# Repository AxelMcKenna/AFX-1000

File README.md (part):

# AFX-1000

**Proprietary — all rights reserved.** Original project code, firmware, PCB and housing designs require a separate written license for reuse, builds, manufacture or redistribution. Public access and build instructions do not grant that permission. Third-party licenses and GitHub's applicable platform permissions remain in effect. See [LICENSE](LICENSE) and [dependency notices](THIRD_PARTY_NOTICES.md).

**AFX-1000** is an RMX-1000-inspired effects processor built around a shared C++20 audio engine, available as a native Mac app, AU and VST3. The standalone hardware design uses **Daisy Seed 3 and two main custom PCBs**—signal and power/protection—in a proposed custom housing.

Use it with rekordbox through app capture or an audio interface. The effects and factory drums are original implementations. Matching the reference unit's sound, timing and full feature set is still work in progress.

## What's in it

- **Scene FX:** BPF Echo, Echo, Noise, Spiral Up, Reverb Up, HPF Echo, LPF Echo, Crush Echo, Spiral Down and Reverb Down.
- **Isolate FX:** three bands, with Isolator, Cut/Add, Trans/Roll and Gate/Drive modes.
- **X-Pad:** four internal drums and four sample banks, 16 bank variants, WAV import, pitch, rolls, hold and overdub.
- **Release FX:** Back Spin, Echo and Vinyl Brake.

Auto BPM, tap tempo, quantized rolls, assignable X-Pad divisions including triplets, MIDI learn, soft takeover and DAW automation are included.

Loop tempo and pitch have separate playback controls. AUTO can follow detected beat phase, and MIDI clock supports Start, Stop, Continue and Song Position Pointer. See [sync](docs/synchronization.md) and [sample stretching](docs/sample-stretching.md) for the implementation limits.

Overdub runs a four-beat pattern. Each bank holds 16 seconds of audio; slot 1 supports BPM-tagged loops. Sample editing includes trim, reverse, normalization and BPM/loop settings. Pad one-shots trigger immediately.

### Latest sound pass

Rebuilt kick, snare, clap and hat voices, with independent gain, decay and envelope choices. Noise now has a resonant filter sweep, shaped modulation and a damped echo return. Faster pitched playback uses a band-limited reader; a linked stereo peak limiter catches output overshoots.

Pitch travel has separate up/down ranges from 1 to 24 semitones. The extra range is a project extension. These changes are implemented, but have not been matched against recordings of an RMX-1000. [DSP notes](docs/dsp-model.md) cover the details and limits.

## Current hardware: two main PCBs

The current standalone design consolidates the earlier eight main boards into **two main custom PCBs**:

- **Signal main:** audio, converter interface, the retained **Daisy Seed 3** module, controls and LED drivers.
- **Power/protection:** supply conversion, inlet and rail protection, monitoring, negative-rail startup and fan health, on a C-shaped board that wraps around the signal-board allocation.

Panel boards and bought-in modules are additional; “two boards” describes the main PCB assembly, not every board in the unit.

**Daisy Seed 3 is retained.** It mounts on the signal PCB in a 40-pin socket. The redesign combines the surrounding audio/control and power/protection circuits into the two main boards.

**The current design is in development and is not ready for fabrication.** The integrated schematics and partial routing are available in KiCad; routing, the ESS codec footprint, manufacturing choices and complete installed housing fit remain unfinished.

| Current board | Functions | Overall size | Checked routing status |
| --- | --- | --- | --- |
| [Signal main](hardware/fabrication/staging/two-board-signal-routed-native-03/signal_main.kicad_pro) | Audio, converter interface, Daisy processor, controls and LED drivers | 268 × 63 mm | 251 open connections; zero geometry/ERC findings; missing ESS codec footprint |
| [Power/protection](hardware/fabrication/staging/two-board-power-monitor-return-planes-native-01/power_protection.kicad_pro) | 12 V supply, inlet, rail protection, monitoring, negative-rail startup and fan health | 320 × 181.1 mm | 2,037 open connections; zero geometry/parity/ERC errors; two retained isolated-reference warnings |

The signal PCB has 466 placed electrical footprints and one unplaced ESS codec. The power PCB has 1,086 electrical components. The latest verified working candidate, **TBP67**, closes five ground connections, including the last four surveyed SN74 logic ground pins. All 75 surveyed SN74 grounds now reach the main ground group. Its audit preserves **2,401 existing reference checks**, all seven quiet-ground networks and nine supply fields. The two DC-input sheets change around fifteen ground vias; their conditional paired resistance rises by 0.6246%, without establishing a current/thermal rating. Four older connector-end reference gaps remain. Across AUX, 73 of 81 IC supply pins still lack regulator connections. See the [TBP67 evidence](hardware/fabrication/staging/two-board-power-monitor-return-planes-native-01/final-review.json); [status-50](hardware/fabrication/staging/two-board-fabrication-status-50/status.json) is an earlier recorded checkpoint.

### Current PCB layouts

These are native KiCad exports of the current copper layouts, with incomplete routing and return paths. The power preview shows TBP67 bottom copper; the linked inner layers contain the updated ground references. Click either image for its native SVG; other layers are linked below.

**Signal main — Daisy Seed 3 and audio/control circuitry**

[Bottom copper](hardware/fabrication/staging/two-board-signal-routed-native-03/plots/back.png) · [All layers and signal-board evidence](hardware/fabrication/staging/two-board-signal-routed-native-03/README.md)

**Power/protection — C-shaped board, TBP67 control routing and ground returns**

[Front copper](hardware/fabrication/staging/two-board-power-monitor-return-planes-native-01/plots/front.png) · [Bottom copper](hardware/fabrication/staging/two-board-power-monitor-return-planes-native-01/plots/back.png) · [All layers and power-board evidence](hardware/fabrication/staging/two-board-power-monitor-return-planes-native-01/README.md)

### Housing and fabrication status

Start with the [print-first kit](hardware/cad/two_board_print_02/TBH01-r6-print-first-kit.zip) and [print order](hardware/cad/two_board_print_02/README.md): test the four core coupons, then print the tray before the lid. The minimum case uses three one-piece parts or twelve split pieces.

The current [TBH01 r6 housing package](hardware/cad/two_board_print_01/README.md) is available for an **unpowered fit prototype**, with 67 checked STL designs, actual PCB supports, a removable lid and bolted split parts. [Download the print package](hardware/cad/two_board_print_01/TBH01-r6-print-package.zip). The largest split part is **175 × 192.4 × 43.6 mm**, before brim. Printer compatibility and print duration require the actual printer and material.

**Current housing CAD renders** — generated from the delivered r6 STL geometry. Controls and fasteners are omitted; these views show the unpowered fit prototype.

| Rear connector panel | Open shell and PCB supports |
| --- | --- |
|  |  |

[Housing and two-board placement overview](hardware/cad/two_board_print_01/preview-r6.png)

For the lever, use the [TBH03-r5 retention add-on](hardware/cad/two_board_print_03/TBH03-lever-retention-r5.zip) and its [assembly instructions](hardware/cad/two_board_print_03/README.md). Its replacement bracket and removable bearing cap replace the original r6 lever bracket and provide a checked rigid assembly path. Fourteen delivered STLs, fifteen clearance/assembly checks and four retention/stop checks pass independent review. The housing and lever arm remain unchanged.

Selector/display/LED/sensor carriers, lever spring and magnet retention, harness integration and operating cooling remain unfinished. The CAD supports use the TBP61 placement snapshot; TBP62–66 preserve those board outlines, mounts and component positions. Both boards use a provisional eight-layer template; the manufacturing stack is not accepted.

Remaining work includes full routing and current returns, approved ESS package/land/stencil inputs, loaded power and startup checks, AUX distribution, installed thermal and assembly qualification, exact BOM and reviewed manufacturing outputs. The [latest power-board review](hardware/fabrication/staging/two-board-power-monitor-return-planes-native-01/README.md) records the current checks; the [fabrication inventory](hardware/fabrication/README.md) retains detailed engineering history.

The [standalone firmware candidate](hardware/firmware/full_engine/README.md) builds the shared DSP engine with 152 parameters, bounded SDRAM storage and control-fault recovery. Full-unit hardware operation remains to be qualified.

## Run it

Requires macOS 12+, Xcode Command Line Tools and CMake 3.24+. The default native app needs no third-party SDK. Ableton Link is optional and disabled by default.

```sh
git clone git@github.com:AxelMcKenna/afx-1000.git
cd afx-1000
./build-app.sh
open build/RMX.app
```

**Cmd+,** opens audio setup. Pick an input and output, then start audio.

Audio setup remembers devices, channel pairs and buffer size. A previously active route can resume on launch when its devices are available. **Stop Audio** disables that automatic resume.

**Space** bypasses. **Esc** resets the effects. **T** taps tempo. **1-4** trigger the pads. Hold **Shift** while dragging for fine adjustments.

### With rekordbox

On macOS 14.2+, select **rekordbox - direct app capture** as the RMX input and choose your speakers or headphones as the output. Start audio, approve macOS capture access if prompted, then play a track in rekordbox.

The capture route mutes duplicate dry playback while active. Stopping it restores normal rekordbox playback. The AU/VST3 versions are for plugin hosts; rekordbox integration uses audio routing.

For an FLX4 or FLX6 with an audio interface:

```text
FLX master RCA -> Interface inputs -> RMX -> Interface outputs -> Speakers
rekordbox cue  -> FLX headphones
```

Physical FLX routing and cue separation still need testing. BlackHole and mixer send/return setups are covered in the [routing guide](docs/routing.md).

## Repository layout

| Directory | Purpose |
| --- | --- |
| `src/`, `include/` | Shared audio engine, public headers and native/plugin adapters |
| `firmware/`, `hardware/` | Embedded targets, electronics, mechanics and qualification evidence |
| [`tools/`](tools/README.md) | Audio tools grouped by effect, C++ probes, command-line utilities and packaging |
| [`tests/`](tests/README.md) | Separate core, audio, hardware, packaging and tooling suites |
| `research/` | Investigations, experiment sources and recorded measurements |
| `docs/`, `assets/`, `prototypes/` | Guides and review records, product assets and earlier UI prototypes |

Former source paths are listed in the [migration index](docs/path-migrations.json). Build outputs and large local artifacts remain under ignored `build*/` directories.

## Build

### Python tooling

Install [uv](https://docs.astral.sh/uv/getting-started/installation/), then run from the repository root:

```sh
uv sync --locked
uv run --locked python -m unittest discover -s tests/tooling
uv run --locked python -m unittest discover -s tests/hardware -p 'a*_integration_tests.py'
```

uv uses Python 3.12 from `.python-version` and creates an ignored `.venv/`. The root `pyproject.toml` declares NumPy, Pillow, SciPy, Shapely and trimesh; `uv.lock` pins the resolved environment. Run Python tools with `uv run --locked python ...`. Use `uv add <package>==<version>` to change a pinned dependency, and commit both project metadata and the lockfile.

Configure CMake through `uv run --locked cmake ...` so its Python tests use this environment. An existing CMake build may retain a previously selected interpreter; use a fresh build directory or explicitly set `-DPython3_EXECUTABLE=/absolute/path/to/.venv/bin/python` when reconfiguring.

The six hardware `requirements.txt` files remain frozen dependency snapshots referenced by historical source hashes. New development and CI use the root uv project. OpenSCAD, KiCad and the ARM toolchain remain separate native dependencies; checks that need KiCad's `pcbnew` module still use KiCad's own Python interpreter.

<details>
<summary>AU, VST3 and JUCE standalone</summary>

```sh
cmake -S . -B build-plugins \
  -DCMAKE_BUILD_TYPE=Release \
  -DRMX_BUILD_PLUGINS=ON
cmake --build build-plugins --parallel 4
```

Fetches JUCE 8.0.6. Use `-DRMX_JUCE_PATH=/path/to/JUCE` for a local checkout. Outputs are in `build-plugins/RMXPlugin_artefacts/Release/`.

For a universal Mac build, use a fresh build directory and add `'-DCMAKE_OSX_ARCHITECTURES=arm64;x86_64'`. Distribution signing and notarization need your Apple credentials. The native build script signs ad hoc for local use.

JUCE's license applies to distribution of the plugin builds.

</details>

<details>
<summary>Core, checks and offline rendering</summary>

The core builds on macOS and Linux, independently of the UI.

```sh
uv run --locked cmake -S . -B build -DCMAKE_BUILD_TYPE=Release
cmake --build build --parallel 4
ctest --test-dir build --output-on-failure
./build/rmx_benchmark
./build/rmx_render input.wav output.wav "assets/presets/Spiral Build.rmx"
```

The renderer's preset argument is optional. Benchmarks measure DSP time, not physical audio latency.

To render 21 drum/pitch/roll and Noise audition clips without opening an audio device:

```sh
cmake --build build --target rmx_sound_preview --parallel 4
./build/rmx_sound_preview build/sound-audition
```

Choose a new output directory each time. These clips use the current engine; they are not recordings of the original hardware.

</details>

## Status

| Area | Current state |
| --- | --- |
| Native Mac audio | Direct rekordbox capture and speaker output have worked in a live session. The latest saved-route/restart behavior still needs a live check. |
| AU / VST3 | Build locally. Earlier universal artifacts include Apple Silicon and Intel slices; the latest sound review builds are arm64. Full DAW validation and Intel runtime checks remain open. |
| Engine and firmware | F06 records 16 passing host groups and clean ARM builds for onboard and external-converter profiles. The source snapshot also records five focused sanitizer groups. Actual MCU timing and hardware operation remain unverified. |
| Synchronization | AUTO, tap, host transport and MIDI clock are implemented. Optional Link builds and controlled local peer tempo/phase checks pass; live rekordbox and audio-loopback alignment remain unverified. See [sync](docs/synchronization.md). |
| Sound matching | Latest drum/Noise changes are ready for listening. No reference-unit comparison or claim of identical effects. |
| Live use | Physical FLX4/FLX6 routing, cue separation, a live two-hour soak and measured round-trip latency remain open. |

The engine uses stereo floating-point audio and preallocated processing buffers. The core audio callback does no allocation, locking, file I/O or UI work. Signal checks cover 44.1, 48, 88.2 and 96 kHz. Results belong to the revisions and configurations documented in [validation](docs/validation.md); they do not establish MCU deadlines or hardware-equivalent specifications. See [specifications](docs/specifications.md) for the remaining measurements.

### Earlier hardware variants

The [B1 5 V budget prototype](hardware/budget/README.md) and [A0.2 higher-headroom carrier](hardware/electrical/README.md) are separate, earlier designs. Their board layouts, enclosure files, cost estimates and draft fabrication outputs apply only to those variants. The current two-main-board design is described above; earlier development checkpoints remain in the [fabrication inventory](hardware/fabrication/README.md).

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
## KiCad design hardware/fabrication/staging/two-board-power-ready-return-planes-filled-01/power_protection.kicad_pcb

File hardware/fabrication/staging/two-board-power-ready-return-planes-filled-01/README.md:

# Rejected strict refill export

This directory is diagnostic evidence, not an accepted PCB candidate. The strict
refill check rejected a rounding difference in retained In2.Cu supply zone
`0552f897-fa23-5173-9e85-a8133b7a4048`.

The [native comparison](../two-board-ready-return-planes-refill-diagnosis-01/native-comparison.json)
found no other unexpected retained-zone changes. Boundary displacement was
approximately 1.16 nm and symmetric-difference area was 2.54e-7 mm², with
unchanged component and hole counts. The rounded supply copper was not used.

[Retained-fill output](../two-board-power-ready-return-planes-filled-02/local-plane-fill.json)
keeps all 45 original fills exactly and takes only the two declared ground fills
from this native export. Native checks and independent review are in the
[TBP63 working candidate](../two-board-power-ready-return-planes-native-01/).
No fabrication release is implied.

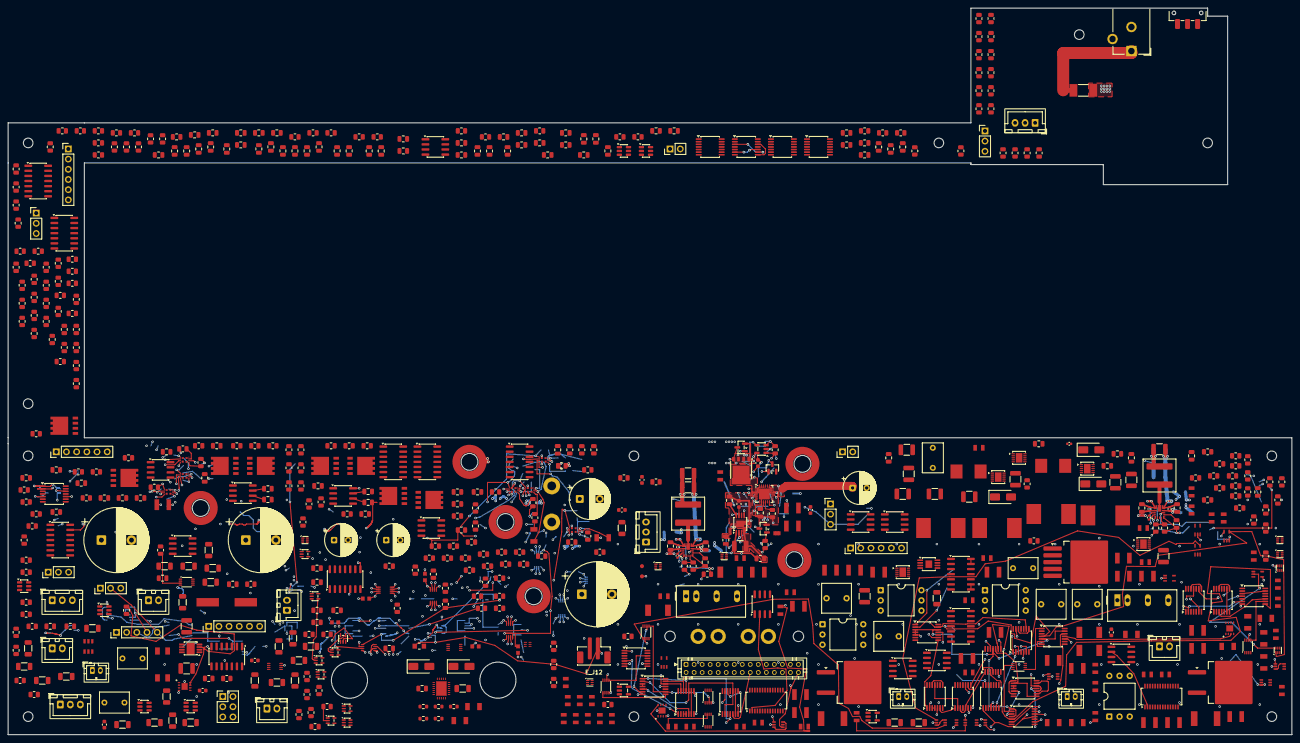
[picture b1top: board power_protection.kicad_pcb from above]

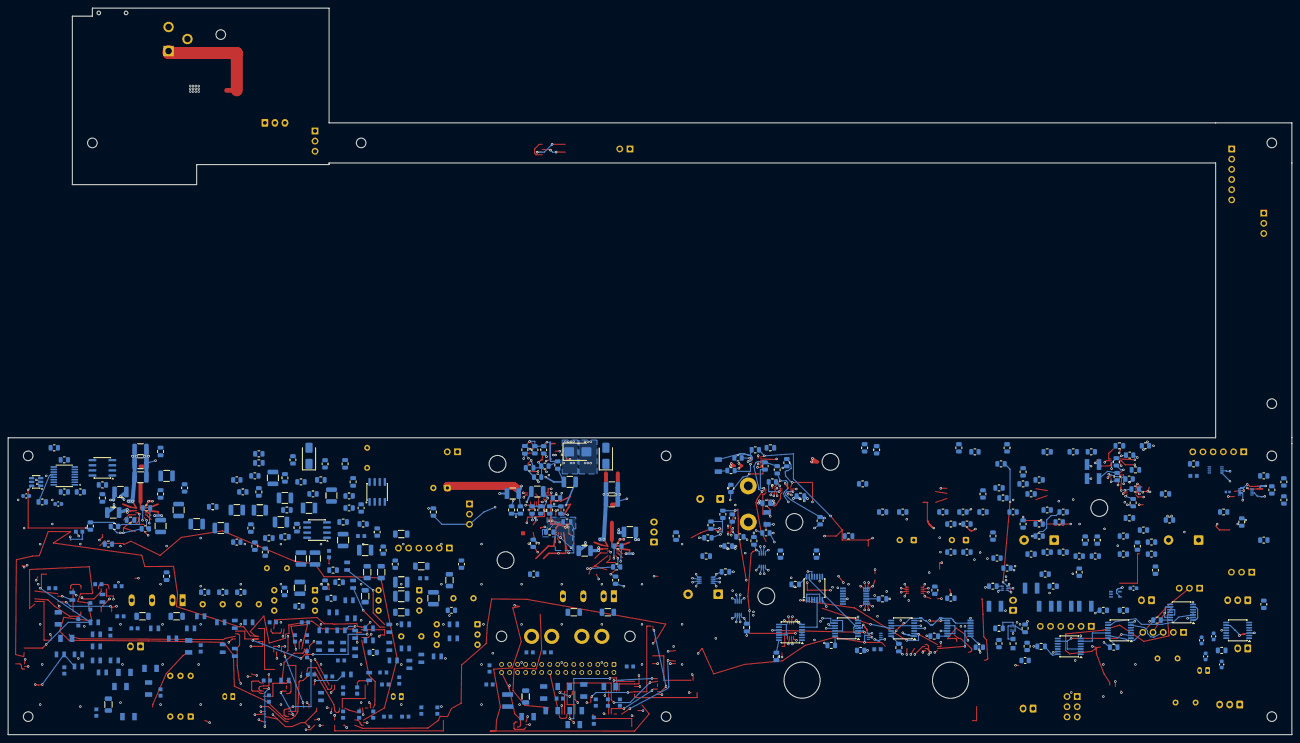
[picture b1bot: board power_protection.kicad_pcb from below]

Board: 8 copper layers, 320.0 x 181.1 mm, 1101 parts (410 on the bottom side), 637 nets.

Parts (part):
E_C1, E_C5, E_C9, E_C13, E_C17, E_C21, E_C25, E_C29, E_C34, E_C35, E_C36, E_C37, E_C57, E_C58, E_C59, E_C66, E_C67, E_C68, E_C69, E_C70, E_C71, E_C72, E_C73, E_C74, E_C75, E_C76, E_C77: 100nF 16V X7R; C_0805_2012Metric
E_C2, E_C3, E_C6, E_C7, E_C10, E_C11, E_C14, E_C15: 10pF 100V C0G 5%; C_0805_2012Metric
E_C4, E_C8: 1500uF 35V electrolytic 20% EEUFR1V152S; CP_Radial_D16.0mm_P7.50mm
E_C12, E_C16: 220uF 35V electrolytic 20% EEUFR1V221; CP_Radial_D8.0mm_P3.50mm
E_C20: 1500uF 16V electrolytic 20% EEUFR1C152; CP_Radial_D10.0mm_P5.00mm
E_C24: 4700uF 16V electrolytic 20% EEUFR1C472; CP_Radial_D16.0mm_P7.50mm
E_C26: 1uF 16V X7R; C_0805_2012Metric
E_C27, E_C28, E_C30, E_C31, E_C32, E_C33, E_C53, E_C54, E_C55, E_C56: 100pF 50V C0G 5%; C_0805_2012Metric
E_C38: 10uF 16V X7R; C_0805_2012Metric
E_C39, E_C41, E_C49, E_C61, E_C62, E_C63, E_C64, E_C65: 100nF 50V C0G 5% C1210C104J5GACTU; KEMET_C1210_LevelB
E_C40, E_C42, E_C44, E_C46, E_C48, E_C50, E_C52: 1uF 50V X7R; C_0805_2012Metric
E_C43, E_C45, E_C47, E_C51: 47nF 50V C0G 5% C1206C473J5GACTU; KEMET_C1206_LevelB
E_C60: 10nF 50V C0G 5%; C_0805_2012Metric
E_C78, E_C80, E_C81, E_C82, E_C83, E_C84, E_C85: 100nF 16V X7R 10% KEMET C0603C104K4RACTU; KEMET_C0603_LevelB
E_C79: 100nF 16V X7R 10% KEMET C0402C104K4RACTU; KEMET_C0402_LevelB
E_C86: 100nF 50V X7R C0603C104K5RACTU; AX03_C0603
E_J1, E_J3: Header6; PinHeader_1x06_P2.54mm_Vertical
E_J4: Alpha3079_AWG14_DIG_FORCE; AWG14_Force_2x1_P9mm_Engineering
E_J5, E_J6: Header3; PinHeader_1x03_P2.54mm_Vertical
E_J7, E_J8, E_J10, E_J11: 7466003R; 7466003R_M3_SMT_Annulus_NPTH
E_J9: E28 CONTROL; PinHeader_1x05_P2.54mm_Vertical
E_J12: JST B2B-PH-SM4-TB(LF)(SN); JST_B2B_PH_SM4_TB_MechanicalLands
E_Q1, E_Q2, E_Q3, E_Q4, E_Q5, E_Q6, E_Q7, E_Q8: CSD18540Q5B; CSD18540Q5B_TI_Q5B
E_R1, E_R9, E_R17, E_R25: 22 1%; R_0805_2012Metric
E_R2, E_R10, E_R18, E_R26, E_R60, E_R63, E_R68, E_R71, E_R76, E_R81, E_R86, E_R91: 20M 1%; R_0805_2012Metric
E_R3, E_R5, E_R11, E_R13, E_R19, E_R21, E_R27, E_R29, E_R61, E_R64, E_R69, E_R72, E_R77, E_R82, E_R87, E_R92: 10k 1%; R_0805_2012Metric
E_R4, E_R12, E_R20, E_R28, E_R98, E_R102, E_R106, E_R110, E_R114, E_R118, E_R122: 100 1%; R_0805_2012Metric
E_R6, E_R7, E_R14, E_R15, E_R22, E_R23, E_R30, E_R31: 15k 1%; R_0805_2012Metric
E_R8, E_R16, E_R24, E_R32, E_R40, E_R48: 47k 1%; R_0805_2012Metric
E_R49: 150k 0.01% 5ppm; R_0805_2012Metric
E_R50: 6.2k 0.01% 5ppm; R_0805_2012Metric
E_R51, E_R54, E_R58, E_R59, E_R62, E_R66, E_R67, E_R70, E_R74, E_R75, E_R79, E_R80, E_R84, E_R85, E_R89, E_R90, E_R94, E_R124, E_R127, E_R130, E_R133: 10k 0.01% 5ppm; R_0805_2012Metric
E_R52, E_R55: 1k 1%; R_0805_2012Metric
E_R53: 100k 0.01% 5ppm; R_0805_2012Metric
E_R56: 143k 0.01% 5ppm; R_0805_2012Metric
E_R57: 3.3k 0.01% 5ppm; R_0805_2012Metric
E_R65: 90.9k 0.01% 5ppm; R_0805_2012Metric
E_R73, E_R78: 31.6k 0.01% 5ppm; R_0805_2012Metric
E_R83: 12.4k 0.01% 5ppm; R_0805_2012Metric
E_R88: 7.5k 0.01% 5ppm; R_0805_2012Metric
E_R93: 200k 0.1% ERA6AEB204V - COMPLETE1% RECEIVING; R_0805_2012Metric
E_R95, E_R99, E_R103, E_R107, E_R111, E_R115, E_R119, E_R125, E_R128, E_R131, E_R134, E_R136, E_R141: 10k; R_0805_2012Metric
E_R96, E_R100, E_R104, E_R108, E_R112, E_R116, E_R120, E_R140: 47k; R_0805_2012Metric
E_R97, E_R101, E_R117: 2.43k 0.1%; R_0805_2012Metric
E_R105, E_R109, E_R113, E_R121: 604 0.1%; R_0805_2012Metric
E_R123, E_R126, E_R129, E_R132: 28.7k 0.01% 5ppm; R_0805_2012Metric
E_R135: 10k 0.1% 25ppm Panasonic ERA6AEB103V; Resistor_SMD_Panasonic_ERA6A_2012
E_R137: 11.1k 0.1%; R_0805_2012Metric
E_R138: 39.2 0.1%; R_0805_2012Metric
E_R139: 10k 0.1%; R_0805_2012Metric
E_R142: 15k; R_0805_2012Metric
E_R143: 15k 0.1% 25ppm Panasonic ERA6AEB153V; Resistor_SMD_Panasonic_ERA6A_2012
E_U1, E_U2, E_U3, E_U4: SI8751AB-ISR; SOIC-8_3.9x4.9mm_P1.27mm
E_U7: REF35125QDBVR; SOT-23-6
E_U8: OPA2333AID; SOIC-8_3.9x4.9mm_P1.27mm
E_U9, E_U10: TLV1824DR; SOIC-14_3.9x8.7mm_P1.27mm
E_U11, E_U12, E_U24, E_U25, E_U26, E_U27: SN74LVC08APWR; TSSOP-14_4.4x5mm_P0.65mm
E_U13, E_U14, E_U15, E_U16, E_U17, E_U32, E_U33: TPS259482LYWP; TPS259482L_YWP0012A
E_U18: TLV1824PWR; TLV1824_PW0014A
E_U19, E_U20: TPS389001DSET; TPS389001_DSE0006A
E_U21, E_U22: SN74LVC02APWR; TSSOP-14_4.4x5mm_P0.65mm
E_U23: SN74LVC32APWR; TSSOP-14_4.4x5mm_P0.65mm
E_U28: SN74LVC14APWR; SN74LVC14A_PW0014A
E_U29, E_U30, E_U31, E_U34: SN74AUP2G08DCUR; SN74AUP2G08_DCU0008A
E_U35, E_U36, E_U37, E_U38, E_U39, E_U40, E_U41: SN74AUP3G17DCUR; SN74LVC3G17_DCU0008A
E_U42: SN74LVC3G17DCUR; SN74LVC3G17_DCU0008A
E_U43: SN74AUP1G17DCKR; AX03_DCK0005A
F_C1, F_C2: 10uF 25V C3225X7R1E106K250AC; Capacitor_SMD__C_1210_3225Metric
F_C3, F_C14, F_C22, F_C23: 10nF 50V C0G C1206C103J5GACTU; Capacitor_SMD__C_1206_3216Metric
F_C4, F_C5, F_C6, F_C8, F_C9, F_C10, F_C11, F_C12, F_C13, F_C15, F_C16, F_C17, F_C18, F_C19, F_C24: 100nF 25V C0G C1206C104J3GACTU; Capacitor_SMD__C_1206_3216Metric
F_C7: 2.7nF 50V C0G5% C0603C272J5GACTU; Capacitor_SMD__C_0603_1608Metric
F_C20, F_C21: 15pF 50V C0G5% C0603C150J5GACTU; Capacitor_SMD__C_0603_1608Metric
F_C201, F_C202, F_C301, F_C302: 100nF25V C0G5% C1206C104J3GACTU; Capacitor_SMD__C_1206_3216Metric
F_C203, F_C303: 1uF63V10% WIMA MKS2C041001F00KSSD; Capacitor_THT__C_Rect_L7.2mm_W5.0mm_P5.00mm
F_C401, F_C402, F_C403, F_C404: 100nF50V X7R10% C0603C104K5RACTU - EFFECTIVE60nF_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; Capacitor_SMD__C_0603_1608Metric
F_J2, F_J3, F_J4, F_J201: JST B2B-XH-A / XHP-2 / SXH-001T-P0.6; Connector_JST__JST_XH_B2B-XH-A_1x02_P2.50mm_Vertical
F_J5: AVRISP2x3 target-powered3.3V sense ONLY; Connector_PinHeader_2.54mm__PinHeader_2x03_P2.54mm_Vertical
F_J202, F_J203: JST B3B-XH-A / XHP-3 / SXH-001T-P0.6; Connector_JST__JST_XH_B3B-XH-A_1x03_P2.50mm_Vertical
F_J401: JST B2B-PH-K-S / PHR-2 / SPH-002T-P0.5S; Connector_JST__JST_PH_B2B-PH-K_1x02_P2.00mm_Vertical
F_R1, F_R16, F_R17, F_R21, F_R23: 1k 0.1%25ppm TNPW08051K00BEEA; Resistor_SMD__R_0805_2012Metric
F_R2, F_R6, F_R10, F_R13, F_R202, F_R302: 10k 0.1%25ppm TNPW080510K0BEEA; Resistor_SMD__R_0805_2012Metric
F_R3, F_R4, F_R5, F_R7, F_R14, F_R15: 47k 0.1%25ppm TNPW080547K0BEEA; Resistor_SMD__R_0805_2012Metric
F_R8: 68k 0.1%25ppm TNPW080568K0BEEA; Resistor_SMD__R_0805_2012Metric
F_R9: 39k 0.1%25ppm TNPW080539K0BEEA; Resistor_SMD__R_0805_2012Metric
F_R11: 56.2k 0.1%25ppm TNPW080556K2BEEA; Resistor_SMD__R_0805_2012Metric
F_R12, F_R24, F_R201, F_R203, F_R301, F_R303: 100k 0.1%25ppm TNPW0805100KBEEA; Resistor_SMD__R_0805_2012Metric
F_R20, F_R22: 20k 0.1%25ppm TNPW080520K0BEEA; Resistor_SMD__R_0805_2012Metric
F_R401: 220k 0.1%25ppm TNPW0805220KBEEA - COMPLETE1% RECE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; Resistor_SMD__R_0805_2012Metric
F_U1: ATtiny84A-SSUR; Package_SO__SOIC-14_3.9x8.7mm_P1.27mm
F_U2: TPS7A1633DGNR; TI_DGN0008C
F_U3: SN74LVC2G17DCKR; Package_TO_SOT_SMD__SOT-363_SC-70-6
F_U4: TPS3431SDRBR; TI_DRB0008A_TPS3431
F_U5: SN74AUP1G17DCKR; Package_TO_SOT_SMD__SOT-353_SC-70-5
F_U6: SN74LVC1T45DBVR; Package_TO_SOT_SMD__SOT-23-6
F_U7: SN74LVC1G14DCKR; Package_TO_SOT_SMD__SOT-353_SC-70-5
F_U8: SN74LVC1G74DCUR; TI_DCU0008A
F_U9: TPS389001DSET; Package_SON__WSON-6_1.5x1.5mm_P0.5mm
F_U10, F_U11: SN74LVC1G17DCKR; Package_TO_SOT_SMD__SOT-353_SC-70-5
F_U12, F_U13: SN74LVC1G08DCKR; Package_TO_SOT_SMD__SOT-353_SC-70-5
F_U14: SN74LVC1G06DCKR; Package_TO_SOT_SMD__SOT-353_SC-70-5
F_U15: TLP175A(TPL,E); RMX_FH02__TLP175A_11-4M1S_Receiving
F_U16: SN74LVC1G34DCKR; Package_TO_SOT_SMD__SOT-353_SC-70-5
F_U201, F_U301: TPS2553DBVR-1; Package_TO_SOT_SMD__SOT-23-6
F_U401: TPS2553DBVR-1; TI_DBV0006A
F_X1: ABLS-4.000MHZ-12-D4Y-T; RMX_FH02__ABLS_Manufacturer_Land
G_C1: 1uF 50V X7R 10%; C_0805_2012Metric
G_C2: 2.2uF 50V X7R 10%; C_1206_3216Metric
G_C3, G_C4: 100nF25V C0G C1206C104J3GACTU; PROPOSED_KEMET1206_LevelB
G_D1: SMAJ15A-E3/61; D_SMA
G_D2: SS14-E3/61T; D_SMA
G_NT1: MODULE_RETURN_STAR; Return_Star
G_R1, G_R3: 470k 0.1% 25ppm; R_0603_1608Metric
G_R2: 59.0k 0.1% 25ppm; R_0603_1608Metric
G_R4: 43.2k 0.1% 25ppm; R_0603_1608Metric
G_R5: 22.1k 0.1% 25ppm; R_0603_1608Metric
G_U1: TPS26601RHFR; TI_RHF0024A
H_NEW1: PROPOSED_NPTH; H_NEW1
H_NEW2: PROPOSED_NPTH; H_NEW2
H_NEW3: PROPOSED_NPTH; H_NEW3
H_NEW4: PROPOSED_NPTH; H_NEW4
H_NEW5: PROPOSED_NPTH; H_NEW5
H_NEW6: PROPOSED_NPTH; H_NEW6
H_NEW7: PROPOSED_NPTH; H_NEW7
H_NEW8: PROPOSED_NPTH; H_NEW8
H_NEW9: PROPOSED_NPTH; H_NEW9
H_NEW10: PROPOSED_NPTH; H_NEW10
H_NEW11: PROPOSED_NPTH; H_NEW11
H_TOUCH1: PROPOSED_NPTH; H_TOUCH1
H_TOUCH2: PROPOSED_NPTH; H_TOUCH2
I_F1: 045106.3MRL 6.3A 125V; Fuse_Littelfuse-NANO2-451_453
I_J1: PJ-102AH; PJ102AH_RearEdge_E23
I_J3: B3B-XH-A(LF)(SN); JST_XH_B3B-XH-A_1x03_P2.50mm_Vertical
I_S1: JS102011SAQN; JS102011SAQN_RearEdge_E23
M_C1, M_C2, M_C3, M_C4, M_C5, M_C6, M_C7, M_C8, M_C9, M_C10, M_C11, M_C12, M_C13, M_C14, M_C15, M_C16, M_C17, M_C18, M_C19, M_C20, M_C21, M_C22, M_C23, M_C24, M_C25, M_C26, M_C27, M_C28, M_C29, M_C30, M_C31, M_C32, M_C33, M_C34, M_C35, M_C36: 100pF C0G 5%; C_0805_2012Metric
M_C37, M_C38, M_C39, M_C40, M_C41, M_C42, M_C43, M_C44, M_C45, M_C46, M_C47, M_C48: 100nF 16V X7R; C_0805_2012Metric
M_C49: 2.2uF 16V X7R; C_0805_2012Metric
M_C50: 10uF 16V X7R; C_0805_2012Metric
M_C51: 1uF 16V X7R; C_0805_2012Metric
M_J1, M_J3: Conn_01x03; PinHeader_1x03_P2.54mm_Vertical
M_J2: Conn_01x06; PinHeader_1x06_P2.54mm_Vertical
M_J4: Conn_01x02; PinHeader_1x02_P2.54mm_Vertical
M_R1, M_R7, M_R25, M_R31: 91k 0.01% 5ppm; R_0805_2012Metric
M_R2, M_R4, M_R8, M_R10, M_R11, M_R14, M_R16, M_R19, M_R21, M_R22, M_R26, M_R28, M_R32, M_R33, M_R35, M_R36, M_R39, M_R41, M_R44, M_R45, M_R47, M_R48, M_R51, M_R53, M_R56, M_R58, M_R59, M_R62, M_R64, M_R67, M_R69, M_R70, M_R73, M_R75, M_R77, M_R80, M_R82, M_R84, M_R85, M_R88, M_R90, M_R92, M_R96, M_R98, M_R99, M_R103, M_R105, M_R106, M_R108, M_R111: 10k 0.01% 5ppm; R_0805_2012Metric
M_R3: 3.57k 0.01% 5ppm; R_0805_2012Metric
M_R5, M_R12, M_R17, M_R23, M_R29, M_R37, M_R42, M_R49, M_R54, M_R60, M_R65, M_R71, M_R78, M_R86, M_R93, M_R100: 20M 1%; R_0805_2012Metric
M_R6, M_R13, M_R18, M_R24, M_R30, M_R38, M_R43, M_R50, M_R55, M_R61, M_R66, M_R72, M_R79, M_R87, M_R94, M_R101, M_R113: 10k 1%; R_0805_2012Metric
M_R9: 3.01k 0.01% 5ppm; R_0805_2012Metric
M_R15: 3.4k 0.01% 5ppm; R_0805_2012Metric
M_R20: 2.87k 0.01% 5ppm; R_0805_2012Metric
M_R27, M_R95: 11.5k 0.01% 5ppm; R_0805_2012Metric
M_R34: 604 0.01% 5ppm; R_0805_2012Metric
M_R40: 11.3k 0.01% 5ppm; R_0805_2012Metric
M_R46: 412 0.01% 5ppm; R_0805_2012Metric
M_R52, M_R63: 8.2k 0.01% 5ppm; R_0805_2012Metric
M_R57, M_R68: 1.78k 0.01% 5ppm; R_0805_2012Metric
M_R74, M_R81, M_R89: 499 0.01% 5ppm; R_0805_2012Metric
M_R76: 374 0.01% 5ppm; R_0805_2012Metric
M_R83: 127 0.01% 5ppm; R_0805_2012Metric
M_R91: 768 0.01% 5ppm; R_0805_2012Metric
M_R97: 270 0.01% 5ppm; R_0805_2012Metric
M_R102, M_R104: 100k 0.01% 5ppm; R_0805_2012Metric
M_R107, M_R109: 80.6k 0.01% 5ppm; R_0805_2012Metric
M_R110: 105k 0.01% 5ppm; R_0805_2012Metric
M_R112: 100k 1%; R_0805_2012Metric
M_R114: 330k 1%; R_0805_2012Metric
M_U1, M_U2, M_U3, M_U4: TLV1824IDR; SOIC-14_3.9x8.7mm_P1.27mm
M_U5: OPA4192ID; SOIC-14_3.9x8.7mm_P1.27mm
M_U6: REF5025EIDR; SOIC-8_3.9x4.9mm_P1.27mm
M_U7: TPS3808G01DBVR; SOT-23-6
M_U8: TPS3808G33DBVR; SOT-23-6
M_U9, M_U10, M_U11, M_U12: SN74LVC08APWR; TSSOP-14_4.4x5mm_P0.65mm
N_C1: 56nF50V C0G5% C1206C563J5GACTU - COMPLETE10% RECE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; PROPOSED_KEMET1206_LevelB
N_C2: 33nF50V C0G5% C1206C333J5GACTU - COMPLETE10% RECE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; PROPOSED_KEMET1206_LevelB
N_C3, N_C12, N_C39, N_C55, N_C56, N_C57, N_C58, N_C59, N_C60, N_C61, N_C62, N_C63, N_C64, N_C65, N_C66, N_C67, N_C68, N_C69, N_C70, N_C71, N_C72, N_C73, N_C74, N_C75, N_C76, N_C77, N_C78, N_C79, N_C80, N_C81, N_C82, N_C83, N_C84, N_C85, N_C86, N_C87, N_C88: 100nF 50V X7R10% C0603C104K5RACTU - bypass effect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; PROPOSED_KEMET0603_LevelB
N_C4, N_C31: 10uF 25V X7R MODULE INPUT FILTER/EFFECTIVE/INRUSH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; Capacitor_SMD__C_1206_3216Metric
N_C5, N_C32: 1uF 50V X7R MODULE OUTPUT FILTER/EFFECTIVE HOLD; Capacitor_SMD__C_1206_3216Metric
N_C6, N_C33: 1uF 25V X7R LTC4261 local VIN effective HOLD; Capacitor_SMD__C_1206_3216Metric
N_C7, N_C9, N_C11, N_C13, N_C34, N_C36, N_C38, N_C40: 100nF 25V C0G C1206C104J3GACTU; PROPOSED_KEMET1206_LevelB
N_C8, N_C10, N_C35, N_C37: 10nF 50V C0G COMPLETE10% TIMING RECEIVING; PROPOSED_KEMET1206_LevelB
N_C14, N_C15, N_C16, N_C17, N_C18, N_C19, N_C20, N_C21, N_C22, N_C23, N_C24, N_C25, N_C41, N_C42, N_C43, N_C44, N_C45, N_C46, N_C47, N_C48, N_C49: 100nF 50V C0G C1210C104J5GACTU - COMPLETE10% RAMP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; PROPOSED_KEMET1210_LevelB
N_C26, N_C27, N_C50, N_C51: 2.2uF 63V PET5% MKS2C042201K00JSSD - COMPLETE10% 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; Capacitor_THT__C_Rect_L7.2mm_W7.2mm_P5.00mm_FKS2_FKP2_MKS2_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
N_C28, N_C30, N_C52, N_C54: 47nF 50V C0G C1206C473J5GACTU; PROPOSED_KEMET1206_LevelB
N_C29, N_C53: 100nF 50V C0G C1210C104J5GACTU; PROPOSED_KEMET1210_LevelB
N_C89, N_C90, N_C91, N_C93, N_C94, N_C96: 100nF50V X7R10% C0603C104K5RACTU - EFFECTIVE/PDN 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; PROPOSED_KEMET0603_LevelB
N_C92, N_C95: 47nF50V C0G5% C1206C473J5GACTU - COMPLETE6% RECEI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; PROPOSED_KEMET1206_LevelB
N_C97, N_C98: 100nF25V C0G5% C1206C104J3GACTU - COMPLETE6% CT /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; PROPOSED_KEMET1206_LevelB
N_C99: 100nF25V C0G5% C1206C104J3GACTU - COMPLETE6% UVRE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; PROPOSED_KEMET1206_LevelB
N_C100: 100nF50V X7R10% C0603C104K5RACTU - LOCAL_BYPASS_E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; PROPOSED_KEMET0603_LevelB
N_H101, N_H102: STRAIN_POST_2p6_NPTH_RECEIVING
N_J1: NEW NF03C CONTROL/KELVIN INTERFACE - physical con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; NC265_JST_PHD_B30B-PHDSS_2x15_P2.00mm_Vertical
N_J2: N19 NEW FORCE IN/OUT - connector and harness unse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; NC265_NC265_Force2_18AWG_P5_Drill2p2_Land3p8
N_J3: N19 E28 BANK GATE/COMMON CLAMP - physical interfa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; NC265_JST_PH_B2B-PH-K_1x02_P2.00mm_Vertical
N_J4: N12 NEW FORCE IN/OUT - connector and harness unse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; NC265_NC265_Force2_18AWG_P5_Drill2p2_Land3p8
N_J5: N12 E28 BANK GATE/COMMON CLAMP - physical interfa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; NC265_JST_PH_B2B-PH-K_1x02_P2.00mm_Vertical
N_J6: NEW MODULE INPUT ONLY - keyed JST XH2 receiving c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; NC265_JST_XH_B2B-XH-A_1x02_P2.50mm_Vertical
N_Q1, N_Q2: CSD19536KTT; Package_TO_SOT_SMD__TO-263-2
N_R1, N_R2, N_R8, N_R9: 10k; PROPOSED_TNPW0805_IPC28950
N_R3, N_R10: 205000ohm 0.1% TNPW0805205KBEEA - COMPLETE3% RECE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; PROPOSED_TNPW0805_IPC28950
N_R4, N_R11: 499ohm 0.1% TNPW0805499RBEEA - COMPLETE3% RECEIVI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; PROPOSED_TNPW0805_IPC28950
N_R5, N_R12, N_R95, N_R98, N_R99: 10000ohm 0.1% TNPW080510K0BEEA - COMPLETE3% RECEI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; PROPOSED_TNPW0805_IPC28950
N_R6, N_R7, N_R13, N_R14: 220ohm COMPLETE +/-3% RECEIVING; PROPOSED_TNPW0805_IPC28950
N_R15, N_R16, N_R17, N_R18, N_R19, N_R20, N_R21, N_R22: 47k 3% TOTAL RECEIVING; PROPOSED_TNPW0805_IPC28950
N_R23: 160000ohm COMPLETE0.1% RECEIVING; PROPOSED_TNPU0805_IPC28950
N_R24, N_R41, N_R63, N_R65, N_R80, N_R82: 10k COMPLETE0.1% RECEIVING; PROPOSED_TNPU0805_IPC28950
N_R25, N_R49: 8660ohm COMPLETE0.1% RECEIVING; PROPOSED_TNPU0805_IPC28950
N_R26, N_R50: 35.7ohm COMPLETE0.1% RECEIVING; PROPOSED_TNPU0603_IPC28950
N_R27, N_R31, N_R35, N_R44, N_R47, N_R51: 100k COMPLETE0.1% RECEIVING; PROPOSED_TNPU0805_IPC28950
N_R28, N_R32, N_R36, N_R37, N_R38, N_R39, N_R45, N_R48, N_R52, N_R53, N_R54, N_R55, N_R59, N_R76: 10k COMPLETE3% RECEIVING; PROPOSED_TNPW0805_IPC28950
N_R29, N_R46: 2000ohm COMPLETE0.1% RECEIVING; PROPOSED_TNPU0805_IPC28950
N_R30: 40.2ohm COMPLETE0.1% RECEIVING; PROPOSED_TNPU0603_IPC28950
N_R33: 6040ohm COMPLETE0.1% RECEIVING; PROPOSED_TNPU0805_IPC28950
N_R34: 75ohm COMPLETE0.1% RECEIVING; PROPOSED_TNPU0603_IPC28950
N_R40: 102000ohm COMPLETE0.1% RECEIVING; PROPOSED_TNPU0805_IPC28950
N_R42: 10700ohm COMPLETE0.1% RECEIVING; PROPOSED_TNPU0805_IPC28950
N_R43: 169ohm COMPLETE0.1% RECEIVING; PROPOSED_TNPU0805_IPC28950
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
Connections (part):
/E_rail_disconnect/5V_DIG_OV_OK: E_R81.1, E_R82.2, E_U10.1, E_U37.6
/E_rail_disconnect/5V_DIG_OV_OK_SCHMITT: E_U11.10, E_U37.2
/E_rail_disconnect/5V_DIG_OV_REF: E_R80.2, E_R81.2, E_U10.7
/E_rail_disconnect/5V_DIG_OV_SENSE: E_C33.1, E_R78.2, E_R79.1, E_U10.6
/E_rail_disconnect/ANA_OUTPUT_OK: E_R131.2, E_U18.14, E_U39.3
/E_rail_disconnect/ANA_OUTPUT_OK_SCHMITT: E_U24.4, E_U39.5
/E_rail_disconnect/ANA_PG0: E_R95.1, E_U13.3, E_U41.3
/E_rail_disconnect/ANA_PG0_SCHMITT: E_U31.2, E_U41.5
/E_rail_disconnect/ANA_PG1: E_R99.1, E_U14.3, E_U41.6
/E_rail_disconnect/ANA_PG1_SCHMITT: E_U34.6, E_U41.2
/E_rail_disconnect/ANA_PG2: E_R115.1, E_U32.3, E_U42.1
/E_rail_disconnect/ANA_PG2_SCHMITT: E_U26.10, E_U42.7
/E_rail_disconnect/ANA_SOURCE_OK: E_R125.2, E_U18.2, E_U38.6
/E_rail_disconnect/ANA_SOURCE_OK_SCHMITT: E_U24.1, E_U38.2
/E_rail_disconnect/DIG_OUTPUT_OK: E_R134.2, E_U18.13, E_U39.6
/E_rail_disconnect/DIG_OUTPUT_OK_SCHMITT: E_U24.5, E_U39.2
/E_rail_disconnect/DIG_PG0: E_R103.1, E_U15.3, E_U40.1
/E_rail_disconnect/DIG_PG0_SCHMITT: E_U29.6, E_U40.7
/E_rail_disconnect/DIG_PG1: E_R107.1, E_U16.3, E_U40.3
/E_rail_disconnect/DIG_PG1_SCHMITT: E_U30.2, E_U40.5
/E_rail_disconnect/DIG_PG2: E_R111.1, E_U17.3, E_U40.6
/E_rail_disconnect/DIG_PG2_SCHMITT: E_U34.1, E_U40.2
/E_rail_disconnect/DIG_PG3: E_R119.1, E_U33.3, E_U41.1
/E_rail_disconnect/DIG_PG3_SCHMITT: E_U26.9, E_U30.6, E_U41.7
/E_rail_disconnect/DIG_SOURCE_OK: E_R128.2, E_U18.1, E_U39.1
/E_rail_disconnect/DIG_SOURCE_OK_SCHMITT: E_U24.2, E_U39.7
/E_rail_disconnect/E28_ALL_CHANNELS_READY: E_U26.8, E_U26.12
/E_rail_disconnect/E28_ANA_0_DVDT: E_R98.1, E_U13.7
/E_rail_disconnect/E28_ANA_0_DVDT_CAP: E_C39.1, E_R98.2
/E_rail_disconnect/E28_ANA_0_ILM: E_R97.1, E_U13.9
/E_rail_disconnect/E28_ANA_1_DVDT: E_R102.1, E_U14.7
/E_rail_disconnect/E28_ANA_1_DVDT_CAP: E_C41.1, E_R102.2
/E_rail_disconnect/E28_ANA_1_ILM: E_R101.1, E_U14.9
/E_rail_disconnect/E28_ANA_2_DVDT: E_R118.1, E_U32.7
/E_rail_disconnect/E28_ANA_2_DVDT_CAP: E_C49.1, E_R118.2
/E_rail_disconnect/E28_ANA_2_ILM: E_R117.1, E_U32.9
/E_rail_disconnect/E28_ANA_ENABLE: E_R96.1, E_U13.1, E_U30.3
/E_rail_disconnect/E28_ANA_FOLLOW: E_R100.1, E_U14.1, E_U31.7
/E_rail_disconnect/E28_ANA_FOLLOW2: E_R116.1, E_U32.1, E_U34.3
/E_rail_disconnect/E28_ANA_OUT_SENSE: E_C55.1, E_R129.2, E_R130.1, E_U18.9
/E_rail_disconnect/E28_ANA_SRC_SENSE: E_C53.1, E_R123.2, E_R124.1, E_U18.5
/E_rail_disconnect/E28_ARMED: E_U21.3, E_U21.4, E_U25.9
/E_rail_disconnect/E28_ARM_BAR: E_U21.1, E_U21.6
/E_rail_disconnect/E28_AUX_CT: E_C60.1, E_U19.5
/E_rail_disconnect/E28_AUX_DIV: E_R137.2, E_R138.1
/E_rail_disconnect/E28_AUX_RESET_N: E_U31.5, E_U35.5
/E_rail_disconnect/E28_AUX_RESET_RAW: E_R135.1, E_U19.6, E_U35.3
/E_rail_disconnect/E28_AUX_SENSE: E_R138.2, E_R139.1, E_U19.1
/E_rail_disconnect/E28_DIG_0_DVDT: E_R106.1, E_U15.7
/E_rail_disconnect/E28_DIG_0_DVDT_CAP: E_C43.1, E_R106.2
/E_rail_disconnect/E28_DIG_0_ILM: E_R105.1, E_U15.9
/E_rail_disconnect/E28_DIG_1_DVDT: E_R110.1, E_U16.7
/E_rail_disconnect/E28_DIG_1_DVDT_CAP: E_C45.1, E_R110.2
/E_rail_disconnect/E28_DIG_1_ILM: E_R109.1, E_U16.9
/E_rail_disconnect/E28_DIG_2_DVDT: E_R114.1, E_U17.7
/E_rail_disconnect/E28_DIG_2_DVDT_CAP: E_C47.1, E_R114.2
/E_rail_disconnect/E28_DIG_2_ILM: E_R113.1, E_U17.9
/E_rail_disconnect/E28_DIG_3_DVDT: E_R122.1, E_U33.7
/E_rail_disconnect/E28_DIG_3_DVDT_CAP: E_C51.1, E_R122.2
/E_rail_disconnect/E28_DIG_3_ILM: E_R121.1, E_U33.9
/E_rail_disconnect/E28_DIG_FOLLOW1: E_R108.1, E_U16.1, E_U29.3
/E_rail_disconnect/E28_DIG_FOLLOW2: E_R112.1, E_U17.1, E_U30.7
/E_rail_disconnect/E28_DIG_FOLLOW3: E_R120.1, E_U33.1, E_U34.7
/E_rail_disconnect/E28_DIG_OUT_SENSE: E_C56.1, E_R132.2, E_R133.1, E_U18.11
/E_rail_disconnect/E28_DIG_SRC_SENSE: E_C54.1, E_R126.2, E_R127.1, E_U18.7
/E_rail_disconnect/E28_FAULT: E_J9.4, E_U21.9, E_U21.13, E_U23.5, E_U28.5
/E_rail_disconnect/E28_FAULT_A: E_U23.8, E_U23.12
/E_rail_disconnect/E28_FAULT_ANY: E_U23.11, E_U25.10
/E_rail_disconnect/E28_FAULT_BAR: E_U21.10, E_U21.12
/E_rail_disconnect/E28_MASTER_ENABLE: E_J6.2, E_J9.5, E_R4.1, E_R12.1, E_R20.1, E_R28.1, E_R104.1, E_R141.1, E_U15.1, E_U20.1, E_U20.3, E_U25.13, E_U27.2, E_U29.5, E_U29.7, E_U30.1, E_U30.5, E_U31.1, E_U34.2, E_U34.5
/E_rail_disconnect/E28_NORMAL_OK: E_U22.8, E_U27.8
/E_rail_disconnect/E28_NORMAL_PRE: E_U24.8, E_U27.9
/E_rail_disconnect/E28_NOT_AUX: E_U23.2, E_U28.4
/E_rail_disconnect/E28_NOT_NORMAL_OK: E_U22.10, E_U23.9
/E_rail_disconnect/E28_NOT_OUT_READY: E_U22.13, E_U26.2, E_U26.5
/E_rail_disconnect/E28_NOT_RUN: E_U23.1, E_U28.2, E_U28.9
/E_rail_disconnect/E28_NOT_SOURCE_READY: E_U28.10, E_U28.13
/E_rail_disconnect/E28_OUTPUT_PERMISSION: E_U26.11, E_U27.1
/E_rail_disconnect/E28_OUTPUT_READY: E_J9.3, E_U25.6
/E_rail_disconnect/E28_OUT_ARMED: E_U22.3, E_U22.4, E_U26.1
/E_rail_disconnect/E28_OUT_ARM_BAR: E_U22.1, E_U22.6
/E_rail_disconnect/E28_OUT_READY: E_U22.11, E_U24.6, E_U25.12, E_U26.13
/E_rail_disconnect/E28_OUT_UV_FAULT: E_U23.10, E_U26.3
/E_rail_disconnect/E28_OUT_VALID_ACTIVE: E_U22.2, E_U25.11
/E_rail_disconnect/E28_RESET_OUT: E_U22.5, E_U23.6
/E_rail_disconnect/E28_RUN_AND_SOURCE: E_U24.12, E_U27.6
/E_rail_disconnect/E28_RUN_LOGIC: E_U27.4, E_U28.8
/E_rail_disconnect/E28_SAFE_REQUEST: E_R140.1, E_U12.13, E_U27.11
/E_rail_disconnect/E28_SAFE_STAGE: E_U25.3, E_U27.12
/E_rail_disconnect/E28_SOURCE_READY: E_U24.3, E_U24.9, E_U25.2
/E_rail_disconnect/E28_SOURCE_READY_LOGIC: E_U27.5, E_U27.10, E_U28.12
/E_rail_disconnect/E28_TIMEOUT: E_U26.4, E_U35.7
/E_rail_disconnect/E28_TIMEOUT_CT: E_C61.1, E_C62.1, E_C63.1, E_C64.1, E_C65.1, E_U20.5
/E_rail_disconnect/E28_TIMEOUT_FAULT: E_U23.13, E_U26.6
/E_rail_disconnect/E28_TIMEOUT_RAW: E_R136.1, E_U20.6, E_U35.1
/E_rail_disconnect/E28_USER_AUX: E_U24.11, E_U25.1
/E_rail_disconnect/N12_ALLOW: E_R28.2, E_R29.1, E_U4.3
/E_rail_disconnect/N12_DRIVE: E_R25.1, E_U4.8
/E_rail_disconnect/N12_INV: E_R54.1, E_R55.1, E_U8.7
/E_rail_disconnect/N12_MCAP1: E_C14.2, E_U4.7
/E_rail_disconnect/N12_MCAP1_LIMIT: E_C14.1, E_R30.2
/E_rail_disconnect/N12_MCAP2: E_C15.2, E_U4.6
/E_rail_disconnect/N12_MCAP2_LIMIT: E_C15.1, E_R31.2
/E_rail_disconnect/N12_OV_OK_SCHMITT: E_U11.4, E_U37.7
/E_rail_disconnect/N12_OV_REF: E_R70.2, E_R71.2, E_U9.11
/E_rail_disconnect/N12_SUM: E_R53.2, E_R54.2, E_U8.6
/E_rail_disconnect/N12_TT: E_R27.1, E_U4.2
/E_rail_disconnect/N19_ALLOW: E_R12.2, E_R13.1, E_U2.3
/E_rail_disconnect/N19_DRIVE: E_R9.1, E_U2.8
/E_rail_disconnect/N19_INPUT_MID: E_R49.2, E_R50.1
/E_rail_disconnect/N19_INV: E_R51.1, E_R52.1, E_U8.1
/E_rail_disconnect/N19_MCAP1: E_C6.2, E_U2.7
/E_rail_disconnect/N19_MCAP1_LIMIT: E_C6.1, E_R14.2
/E_rail_disconnect/N19_MCAP2: E_C7.2, E_U2.6
/E_rail_disconnect/N19_MCAP2_LIMIT: E_C7.1, E_R15.2
/E_rail_disconnect/N19_OV_OK_SCHMITT: E_U11.1, E_U36.5
/E_rail_disconnect/N19_OV_REF: E_R62.2, E_R63.2, E_U9.7
/E_rail_disconnect/N19_SUM: E_R50.2, E_R51.2, E_U8.2
/E_rail_disconnect/N19_TT: E_R11.1, E_U2.2
/E_rail_disconnect/NF_VALID_LOGIC: E_U25.5, E_U35.2
/E_rail_disconnect/OK_5: E_U11.8, E_U12.4
/E_rail_disconnect/OK_12: E_U11.6, E_U12.2
/E_rail_disconnect/OK_19: E_U11.3, E_U12.1
/E_rail_disconnect/OK_ALL_OV: E_U12.8, E_U12.12, E_U24.10
/E_rail_disconnect/OK_ANALOG: E_U12.3, E_U12.9
/E_rail_disconnect/OK_AUXILIARY: E_U12.6, E_U12.10
/E_rail_disconnect/OK_REF: E_U11.11, E_U12.5
/E_rail_disconnect/P12_ALLOW: E_R20.2, E_R21.1, E_U3.3
/E_rail_disconnect/P12_COMMON: E_Q5.1, E_Q6.1, E_R18.2, E_U3.5
/E_rail_disconnect/P12_DRIVE: E_R17.1, E_U3.8
/E_rail_disconnect/P12_GATE: E_Q5.2, E_Q6.2, E_R17.2, E_R18.1
/E_rail_disconnect/P12_MCAP1: E_C10.2, E_U3.7
/E_rail_disconnect/P12_MCAP1_LIMIT: E_C10.1, E_R22.2
/E_rail_disconnect/P12_MCAP2: E_C11.2, E_U3.6
/E_rail_disconnect/P12_MCAP2_LIMIT: E_C11.1, E_R23.2
/E_rail_disconnect/P12_OV_OK: E_R68.1, E_R69.2, E_U9.14, E_U36.6
/E_rail_disconnect/P12_OV_OK_SCHMITT: E_U11.5, E_U36.2
/E_rail_disconnect/P12_OV_REF: E_R67.2, E_R68.2, E_U9.9
/E_rail_disconnect/P12_OV_SENSE: E_C31.1, E_R65.2, E_R66.1, E_U9.8
/E_rail_disconnect/P12_TT: E_R19.1, E_U3.2
/E_rail_disconnect/P19_ALLOW: E_R4.2, E_R5.1, E_U1.3
/E_rail_disconnect/P19_COMMON: E_Q1.1, E_Q2.1, E_R2.2, E_U1.5
/E_rail_disconnect/P19_DRIVE: E_R1.1, E_U1.8
/E_rail_disconnect/P19_GATE: E_Q1.2, E_Q2.2, E_R1.2, E_R2.1
/E_rail_disconnect/P19_MCAP1: E_C2.2, E_U1.7
/E_rail_disconnect/P19_MCAP1_LIMIT: E_C2.1, E_R6.2
/E_rail_disconnect/P19_MCAP2: E_C3.2, E_U1.6
/E_rail_disconnect/P19_MCAP2_LIMIT: E_C3.1, E_R7.2
/E_rail_disconnect/P19_OV_OK: E_R60.1, E_R61.2, E_U9.2, E_U36.1
/E_rail_disconnect/P19_OV_OK_SCHMITT: E_U11.2, E_U36.7
/E_rail_disconnect/P19_OV_REF: E_R59.2, E_R60.2, E_U9.5
/E_rail_disconnect/P19_OV_SENSE: E_C30.1, E_R57.2, E_R58.1, E_U9.4
/E_rail_disconnect/P19_SENSE_MID: E_R56.2, E_R57.1
/E_rail_disconnect/P19_TT: E_R3.1, E_U1.2
/E_rail_disconnect/POS_OUTPUT_READY: E_U25.4, E_U27.3
/E_rail_disconnect/REF_HIGH_AUX: E_R88.2, E_R89.1, E_R90.1
/E_rail_disconnect/REF_HIGH_OK: E_R91.1, E_R92.2, E_U10.13, E_U38.3
/E_rail_disconnect/REF_HIGH_OK_SCHMITT: E_U11.13, E_U38.5
/E_rail_disconnect/REF_HIGH_POSITIVE: E_R90.2, E_R91.2, E_U10.11
/E_rail_disconnect/REF_LOW_AUX: E_R83.2, E_R84.1, E_U10.8
/E_rail_disconnect/REF_LOW_OK: E_R86.1, E_R87.2, E_U10.14, E_U38.1
/E_rail_disconnect/REF_LOW_OK_SCHMITT: E_U11.12, E_U38.7
/E_rail_disconnect/REF_LOW_POSITIVE: E_R85.2, E_R86.2, E_U10.9
/E_rail_disconnect/RUN_BUFFERED: E_U28.1, E_U43.4
/E_rail_disconnect/V5_REG_OV_OK: E_R76.1, E_R77.2, E_U10.2, E_U37.3
/E_rail_disconnect/V5_REG_OV_OK_SCHMITT: E_U11.9, E_U37.5
/E_rail_disconnect/V5_REG_OV_REF: E_R75.2, E_R76.2, E_U10.5
/E_rail_disconnect/V5_REG_OV_SENSE: E_C32.1, E_R73.2, E_R74.1, E_U10.4
/F_fan_health_protection/FAN_L_5V: F_C203.1, F_J202.2, F_R202.1, F_R203.1, F_U201.6
/F_fan_health_protection/FAN_L_ILIM: F_R201.1, F_U201.5
/F_fan_health_protection/FAN_L_TACH: F_J202.3, F_R14.1, F_R202.2, F_U3.1
/F_fan_health_protection/FAN_R_5V: F_C303.1, F_J203.2, F_R302.1, F_R303.1, F_U301.6
/F_fan_health_protection/FAN_R_ILIM: F_R301.1, F_U301.5
/F_fan_health_protection/FAN_R_TACH: F_J203.3, F_R15.1, F_R302.2, F_U3.3
/F_fan_health_protection/FAULT_CLK: F_U7.4, F_U8.1
/F_fan_health_protection/HEALTH_AND_WD: F_U12.4, F_U13.1
/F_fan_health_protection/HEARTBEAT: F_R4.1, F_U1.11, F_U16.2
/F_fan_health_protection/HEARTBEAT_FAST: F_U4.6, F_U16.4
/F_fan_health_protection/HW_NOFAULT: F_U11.4, F_U13.2
/F_fan_health_protection/HW_NOFAULT_5: F_R9.1, F_U8.3, F_U11.2
/F_fan_health_protection/ISP_MISO: F_J5.1, F_U1.8
/F_fan_health_protection/ISP_MOSI: F_J5.4, F_U1.7
/F_fan_health_protection/ISP_SCK: F_J5.3, F_U1.9
/F_fan_health_protection/LDO_DELAY: F_C3.1, F_U2.7
/F_fan_health_protection/LEAF_PERMISSION: F_R13.1, F_U13.4, F_U14.2
/F_fan_health_protection/LED_A: F_R1.2, F_R2.1, F_U15.1
/F_fan_health_protection/LED_K: F_R2.2, F_U14.4, F_U15.3
/F_fan_health_protection/MCU_HEALTH: F_R3.1, F_U1.6, F_U12.1
/F_fan_health_protection/MCU_RESET_N: F_J5.5, F_R6.2, F_U1.4
/F_fan_health_protection/MCU_TACH_L: F_R16.2, F_U1.10
/F_fan_health_protection/MCU_TACH_R: F_R17.2, F_U1.5
/F_fan_health_protection/NF_RAW5_ILIM: F_R401.1, F_U401.5
/F_fan_health_protection/RAW_CLEAR_FAST: F_U8.6, F_U10.4
/F_fan_health_protection/RAW_CLEAR_N: F_R10.2, F_U9.6, F_U10.2
/F_fan_health_protection/RAW_POR_CT: F_C14.1, F_U9.5
/F_fan_health_protection/RAW_POR_SENSE: F_R11.2, F_R12.1, F_U9.1
/F_fan_health_protection/TACH_L_BUF: F_R16.1, F_U3.6
/F_fan_health_protection/TACH_R_BUF: F_R17.1, F_U3.4
/F_fan_health_protection/TEMP_L_ADC: F_C22.1, F_R21.2, F_U1.13
/F_fan_health_protection/TEMP_L_NODE: F_J2.1, F_R20.2, F_R21.1
/F_fan_health_protection/TEMP_R_ADC: F_C23.1, F_R23.2, F_U1.12
/F_fan_health_protection/TEMP_R_NODE: F_J3.1, F_R22.2, F_R23.1
/F_fan_health_protection/V3V3: F_C2.1, F_C4.1, F_C5.1, F_C6.1, F_C8.1, F_C9.1, F_C16.1, F_C17.1, F_C18.1, F_C19.1, F_C24.1, F_J5.2, F_R5.1, F_R6.1, F_R7.1, F_R20.1, F_R22.1, F_R24.1, F_U1.1, F_U2.1, F_U3.5, F_U4.1, F_U4.5, F_U5.5, F_U6.1, F_U6.5, F_U11.5, F_U12.5, F_U13.5, F_U14.5, F_U16.5
/F_fan_health_protection/WD_CWD: F_C7.1, F_U4.2
/F_fan_health_protection/WD_EN: F_R7.2, F_U4.3
/F_fan_health_protection/WD_OK: F_R5.2, F_U2.3, F_U4.7, F_U4.8, F_U5.2
/F_fan_health_protection/WD_OK_5: F_R8.1, F_U6.4, F_U7.2
/F_fan_health_protection/WD_OK_FAST: F_U5.4, F_U6.3, F_U12.2
/F_fan_health_protection/XTAL1: F_C20.1, F_U1.2, F_X1.1
/F_fan_health_protection/XTAL2: F_C21.1, F_U1.3, F_X1.2
/G_module_input/MODULE_DVDT: G_C3.1, G_C4.1, G_U1.20
/G_module_input/MODULE_ILM: G_R5.1, G_U1.19
/G_module_input/MODULE_OV: G_R3.2, G_R4.1, G_U1.12
/G_module_input/MODULE_RTN: G_C3.2, G_C4.2, G_R2.2, G_R4.2, G_R5.2, G_U1.15, G_U1.25
/G_module_input/MODULE_UV: G_R1.2, G_R2.1, G_U1.10
/I_input_protection/DC_JACK: I_F1.1, I_J1.1
/M_rail_monitor/5V_DIG_OV_OK: M_R100.1, M_R101.2, M_U4.13, M_U10.13
/M_rail_monitor/5V_DIG_OV_REF: M_C32.1, M_R99.2, M_R100.2, M_U4.11
/M_rail_monitor/5V_DIG_OV_REF_BASE: M_R97.2, M_R98.1, M_R99.1
/M_rail_monitor/5V_DIG_OV_SENSE: M_C31.1, M_R95.2, M_R96.1, M_U4.10
/M_rail_monitor/5V_DIG_UV_OK: M_R93.1, M_R94.2, M_U4.14, M_U10.12
/M_rail_monitor/5V_DIG_UV_REF: M_C30.1, M_R91.2, M_R92.1, M_U4.8
/M_rail_monitor/5V_DIG_UV_RT_MID: M_R88.2, M_R89.1
/M_rail_monitor/5V_DIG_UV_SENSE: M_C29.1, M_R89.2, M_R90.1, M_R93.2, M_U4.9
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

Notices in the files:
README.md:
Assets and licensing:
Original project material is covered by the [AFX-1000 Proprietary Rights Notice](LICENSE), copyright 2026 Axel McKenna, all rights reserved. It covers the project's original software, firmware, legacy prototypes, PCB and mechanical design files, documentation and assets to the extent the owner holds the relevant rights. Reuse, personal builds, manufacture and redistribution require separate written permission, subject to the exceptions in the notice.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
